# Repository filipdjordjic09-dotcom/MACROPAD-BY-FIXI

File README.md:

# Custom 4-Key Macropad with Rotary Encoder

This is my custom DIY Macropad designed for the Hack Club Hackpad program. It features 4 mechanical switches and 1 rotary encoder powered by the Seeed Studio XIAO RP2040 microcontroller running KMK Firmware (CircuitPython).

## 3D Enclosure & CAD Design

## Features
* **Microcontroller:** Seeed Studio XIAO RP2040
* **Keys:** 4x Cherry MX Mechanical Switches (Copy, Paste, Undo, Redo)
* **Rotary Encoder:** EC11 Encoder with built-in push button (Volume Up / Volume Down / Mute)
* **Enclosure:** Custom 3D-printed top shell and bottom lid with M3 screw mounts designed in Onshape
* **Firmware:** KMK Firmware written in CircuitPython

## Bill of Materials (BOM)
| Component | Quantity | Description |
| :--- | :--- | :--- |
| Seeed Studio XIAO RP2040 | 1 | Microcontroller Board |
| Cherry MX Switches | 4 | Mechanical Keyboard Switches |
| EC11 Rotary Encoder | 1 | Encoder with Switch |
| Custom PCB | 1 | Manufactured Gerber PCB |
| Custom 3D Printed Case | 1 | Top Shell & Bottom Lid (.STEP) |
| M3 Screws & Heat-Set Inserts | 4 | Case Assembly |

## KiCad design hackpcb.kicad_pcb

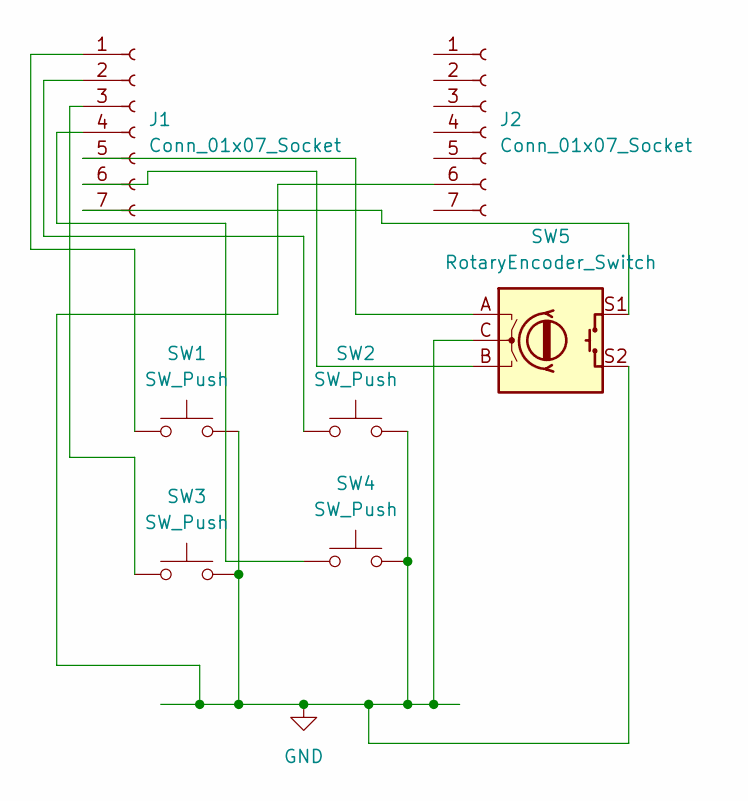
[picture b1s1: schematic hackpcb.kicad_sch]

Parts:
J1, J2: Conn_01x07_Socket; PinSocket_1x07_P2.54mm_Vertical
SW1, SW2, SW3, SW4: SW_Push; SW_Cherry_MX_1.00u_PCB
SW5: RotaryEncoder_Switch; RotaryEncoder_Alps_EC11E-Switch_Vertical_H20mm

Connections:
GND: J2.6 (Pin_6_6), SW1.2, SW2.2, SW3.2, SW4.2, SW5.C, SW5.S2
unnamed: J1.1, SW1.1
unnamed: J1.2, SW2.1
unnamed: J1.3, SW3.1
unnamed: J1.4, SW4.1
unnamed: J1.5, SW5.A
unnamed: J1.6, SW5.B
unnamed: J1.7, SW5.S1

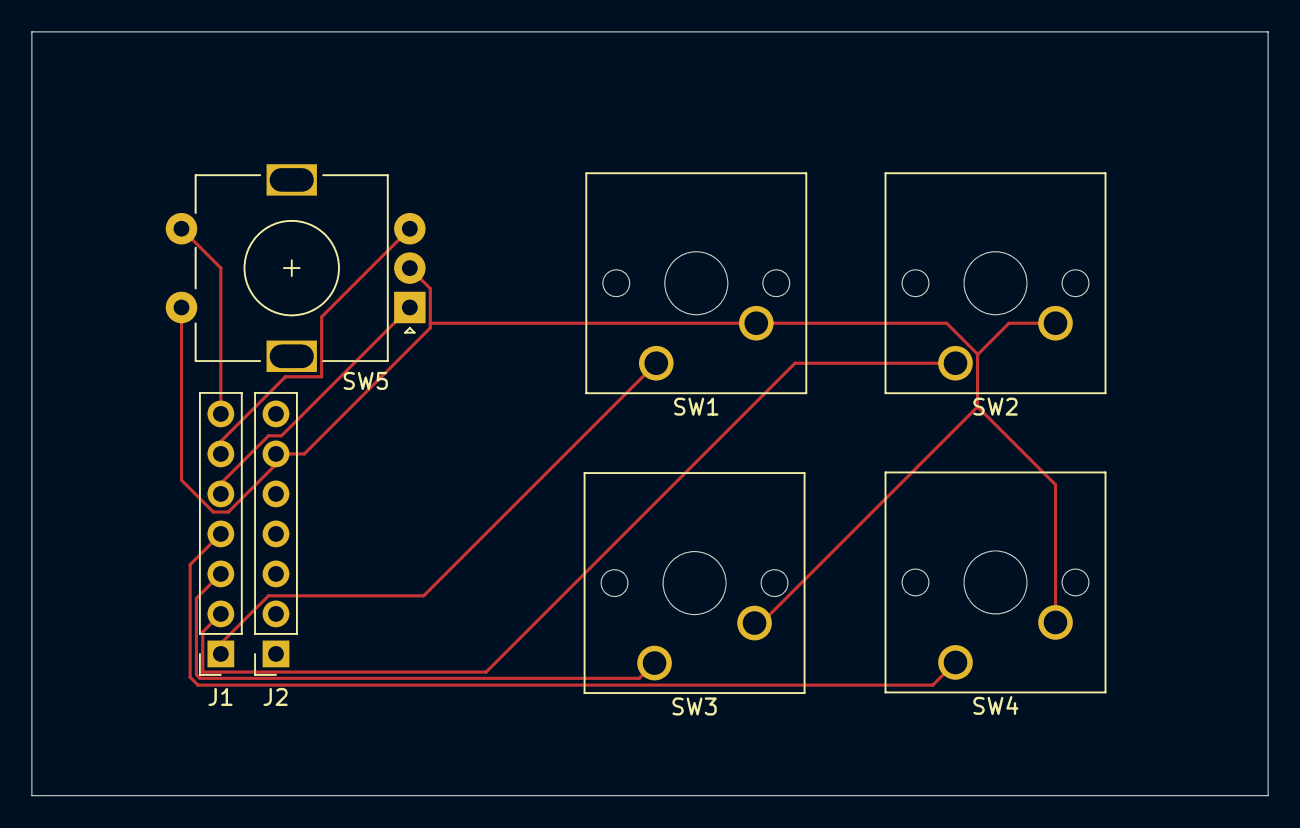
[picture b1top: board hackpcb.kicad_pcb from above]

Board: 2 copper layers, 78.5 x 48.5 mm, 7 parts (0 on the bottom side), 8 nets.
